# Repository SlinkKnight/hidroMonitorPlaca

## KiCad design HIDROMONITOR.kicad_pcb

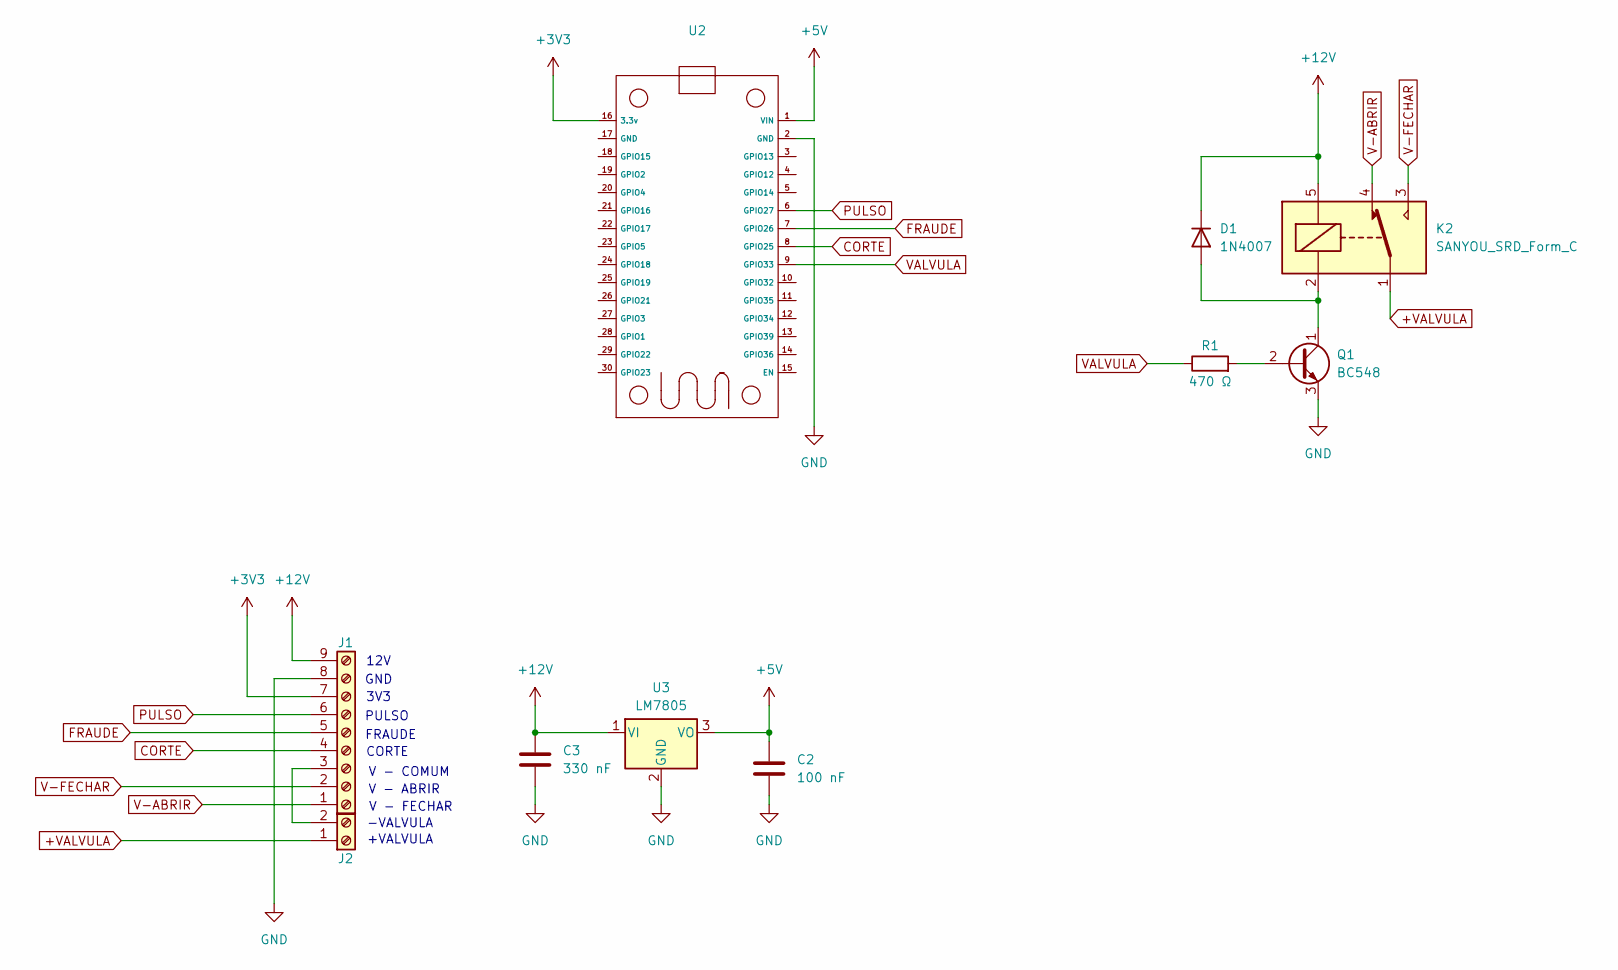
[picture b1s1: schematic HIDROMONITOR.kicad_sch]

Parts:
C2: 100 nF; C_Rect_L7.0mm_W2.5mm_P5.00mm
C3: 330 nF; C_Rect_L7.0mm_W2.5mm_P5.00mm
D1: 1N4007; D_DO-41_SOD81_P10.16mm_Horizontal
J1: Screw_Terminal_01x09; TerminalBlock_Phoenix_MKDS-1,5-9_1x09_P5.00mm_Horizontal
J2: Screw_Terminal_01x02; TerminalBlock_Phoenix_MKDS-1,5-2_1x02_P5.00mm_Horizontal
K2: SANYOU_SRD_Form_C; Relay_SPDT_SANYOU_SRD_Series_Form_C
Q1: BC548; TO-92
R1: 470 Ω; R_Axial_DIN0207_L6.3mm_D2.5mm_P7.62mm_Horizontal
U2: ESP32_30pin
U3: LM7805; TO-220-3_Vertical

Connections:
+3V3: J1.7, U2.16 (3.3v)
+5V: C2.1, U2.1 (VIN), U3.3 (VO)
+12V: C3.1, D1.1 (K), J1.9, K2.5, U3.1 (VI)
+VALVULA: J2.1, K2.1
CORTE: J1.4, U2.8 (GPIO25)
FRAUDE: J1.5, U2.7 (GPIO26)
GND: C2.2, C3.2, J1.8, Q1.3 (E), U2.2 (GND), U3.2 (GND)
unnamed: D1.2 (A), K2.2, Q1.1 (C)
unnamed: J1.3, J2.2
unnamed: Q1.2 (B), R1.2
PULSO: J1.6, U2.6 (GPIO27)
V-ABRIR: J1.1, K2.4
V-FECHAR: J1.2, K2.3
VALVULA: R1.1, U2.9 (GPIO33)

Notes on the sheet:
CORTE
12V
-VALVULA
GND
PULSO
V - FECHAR
FRAUDE
V - COMUM
V - ABRIR
+VALVULA
3V3

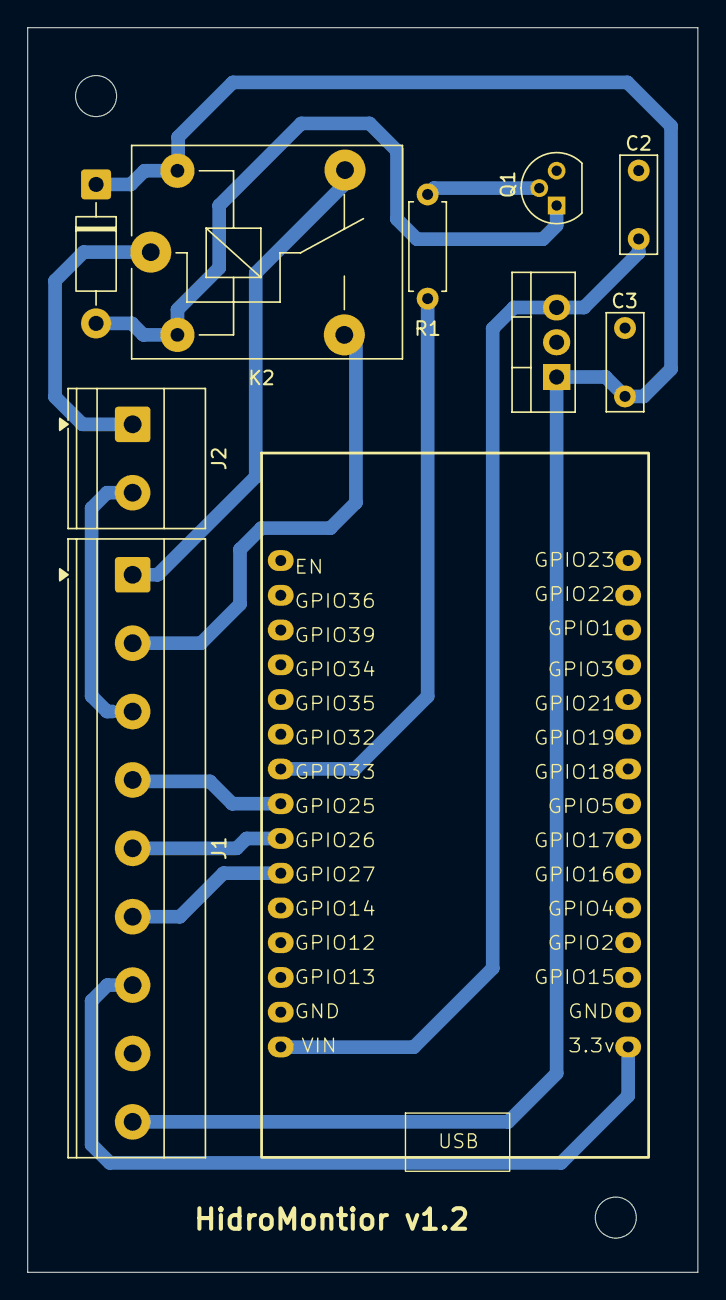
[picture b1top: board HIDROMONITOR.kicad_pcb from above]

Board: 2 copper layers, 49.0 x 91.0 mm, 10 parts (0 on the bottom side), 14 nets.
